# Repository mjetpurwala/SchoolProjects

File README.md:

Project names in each folder

 Baemax: Advanced Embedded Systems Final Project.
   Contents: Pictures and videos of the project and source code

 Alarm Clock: Advanced Embedded Systems Project.
   Contents: Pictures and videos of the project and source code

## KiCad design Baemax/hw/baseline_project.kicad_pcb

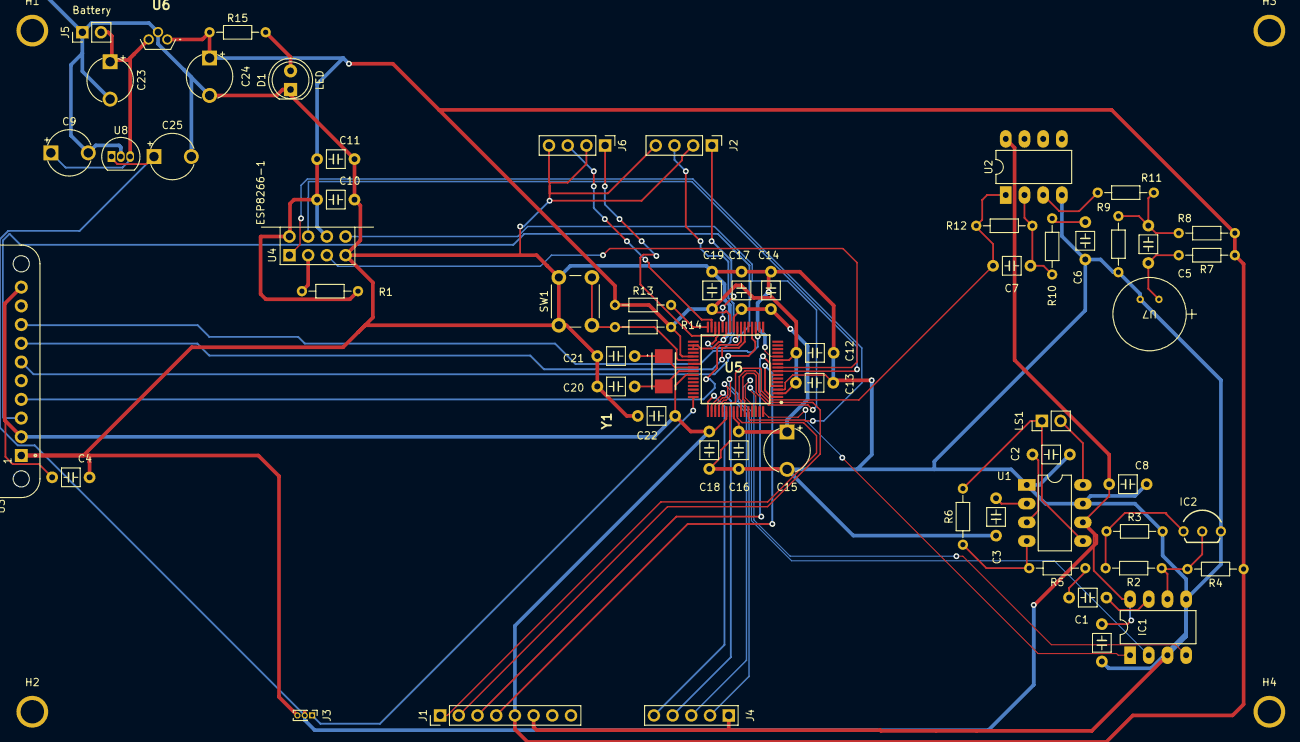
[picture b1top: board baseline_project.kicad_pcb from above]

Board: 2 copper layers, 65 parts (0 on the bottom side), 51 nets.

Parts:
C1, C4, C8, C26: 0.1 uF; C_Axial_200mil
C2: 1.0 uF; C_Axial_200mil
C3, C6: 4.7 uF; C_Axial_200mil
C5: 1u; C_Axial_200mil
C7: 220pF; C_Axial_200mil
C9, C23, C24, C25: 4.7uF; CP_Radial_Tantal200mil
C10: 4.7uF; C_Axial_200mil
C11, C13, C16, C17, C18: 0.1uF; C_Axial_200mil
C12, C19: 0.01uF; C_Axial_200mil
C14, C22: 1uF; C_Axial_200mil
C15: 2.2uF; CP_Radial_Tantal200mil
C20, C21: 10pF C0G; C_Axial_200mil
D1: LED; LED_D5.0mm
H1, H2, H3, H4: MountingHole_4_40
IC1: TLV5616; DIP-8_W7.62mm_LongPads
IC2: LM4041CILPR; ti_LM4041CILPR
J1: Conn_01x06_Pin; PinHeader_1x08_P2.54mm_Vertical
J2, J6: Header_4; PinHeader_1x04_P2.54mm_Vertical
J3: Conn_01x03_Pin; PinHeader_1x03_P1.00mm_Vertical
J4: JTAG; PinHeader_1x05_P2.54mm_Vertical
J5: Battery; PinHeader_1x02_P2.54mm_Vertical
LS1: Speaker; PinHeader_1x02_P2.54mm_Vertical
R1, R7, R14: 10k; R_Axial_DIN0204_L3.6mm_D1.6mm_P7.62mm_Horizontal
R2: 47 kohm; R_Axial_DIN0204_L3.6mm_D1.6mm_P7.62mm_Horizontal
R3, R6: 10 kohm; R_Axial_DIN0204_L3.6mm_D1.6mm_P7.62mm_Horizontal
R4: 2 kohm; R_Axial_DIN0204_L3.6mm_D1.6mm_P7.62mm_Horizontal
R5: 20 kohm; R_Axial_DIN0204_L3.6mm_D1.6mm_P7.62mm_Horizontal
R8, R9: 22k; R_Axial_DIN0204_L3.6mm_D1.6mm_P7.62mm_Horizontal
R10, R11: 1k; R_Axial_DIN0204_L3.6mm_D1.6mm_P7.62mm_Horizontal
R12: 100k; R_Axial_DIN0204_L3.6mm_D1.6mm_P7.62mm_Horizontal
R13: 1M; R_Axial_DIN0204_L3.6mm_D1.6mm_P7.62mm_Horizontal
R15: 330; R_Axial_DIN0204_L3.6mm_D1.6mm_P7.62mm_Horizontal
SW1: Reset; SW_PUSH_6mm
U1: MCP34119P; DIP-8_W7.62mm_LongPads
U2: OPA2350; DIP-8_W7.62mm_LongPads
U3: Adafruit ST7735R; adafruit_st7735r2
U4: ESP8266-1; PinHeader_2x04_P2.54mm_Vertical
U5: TM4C123GH6PMIR; QFP50P1200X1200X160-64N
U6: LP2950-33LPRE3; TL431CLPM
U7: CMA-4544PF-W (elec mic); CMA_CUI_9P7X9P7_CUD
U8: LP2950-5.0_TO92; TO-92_Inline
Y1: ABM3-16.000MHZ-B2-T; ABM3

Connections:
+3V3: C4.1, C10.1, C11.1, C12.1, C13.1, C18.1, C19.1, C22.1, C24.1, J1.5, R1.1, R4.1, R7.1, R8.1, R13.1, R14.1, R15.1, U3.2 (VCC), U3.10 (LITE), U4.6 (Ch_PD), U4.8 (Vcc), U5.2 (VDDA), U5.11 (VDD_1), U5.26 (VDD_2), U5.37 (VBAT), U5.42 (VDD_3), U5.54 (VDD_4), U6.1 (OUTPUT)
+5V: C8.1, C25.1, C26.1, IC1.8 (VDD), J3.2, U1.6 (Vcc), U2.8 (V+), U8.1 (VO)
/LDO: C14.1, C15.1, C16.1, C17.1, U5.25 (VDDC_1), U5.56 (VDDC_2)
/OSC1: C20.1, U5.41 (OSC1), Y1.2
/OSC2: C21.1, U5.40 (OSC0), Y1.1
/Reset: R14.2, SW1.2, U5.38 (~RST)
/TCK: J4.2 (B), U5.52 (PC0/TCK/SWCLK)
/TDI: J4.4 (C), U5.50 (PC2/TDI)
/TDO: J4.5 (C), U5.49 (PC3/TDO/SWO)
/TMS: J4.3 (C), U5.51 (PC1/TMS/SWDIO)
GND: C2.2, C3.2, C4.2, C6.2, C8.2, C9.2, C10.2, C11.2, C12.2, C13.2, C14.2, C15.2, C16.2, C17.2, C18.2, C19.2, C20.2, C21.2, C22.2, C23.2, C24.2, C25.2, C26.2, D1.1 (K), IC1.3 (~CS), IC1.5 (AGND), IC2.3, J1.6, J2.2 (B), J2.4 (C), J3.3, J4.1 (A), J5.1 (A), J6.2 (B), J6.4 (C), R3.2, R9.2, SW1.1, U1.1 (CD), U1.7 (GND), U2.4 (V-), U3.1 (GND), U4.4 (GND), U5.3 (GNDA), U5.12 (GND_1), U5.27 (GND_2), U5.34 (XOSC0), U5.35 (GNDX), U5.39 (GND_3), U5.55 (GND_4), U6.2 (GND), U7.2, U8.2 (GND)
HV: C9.1, C23.1, J5.2 (B), U6.3 (INPUT), U8.3 (VI)
unnamed: C1.2, R5.1
unnamed: C5.1, R7.2, U7.1
unnamed: C5.2, R8.2, R9.1, R11.1
unnamed: C6.1, R10.2
unnamed: D1.2 (A), R15.2
unnamed: C1.1, IC1.7 (OUT)
unnamed: IC1.6 (REF), IC2.2, R2.1, R4.2
unnamed: IC2.1, R2.2, R3.1
unnamed: C2.1, U1.3 (FC1)
unnamed: C3.1, U1.2 (FC2)
unnamed: R5.2, R6.1, U1.4 (VIN)
unnamed: LS1.1, R6.2, U1.5 (VO1)
unnamed: LS1.2, U1.8 (VO2)
unnamed: R11.2, U2.3 (+)
unnamed: C7.1, R10.1, R12.1, U2.2 (-)
unnamed: R1.2, U4.2 (GPIO0)
unnamed: R13.2, U5.32 (~WAKE)
PA2: U3.8 (SCK), U5.19 (PA2/SSI0C1K)
PA3: U3.6 (TFT_CS), U5.20 (PA3/SSI0FSS)
PA5: U3.7 (MOSI), U5.22 (PA5/SSI0TX)
PA6: U3.4 (D/C), U5.23 (PA6)
PA7: U3.3 (RESET), U5.24 (PA7)
PB3: J3.1, U5.48 (PB3/I2C0SDA)
PB4: J1.2, U5.58 (PB4)
PB5: J1.1, U5.57 (PB5)
PB6: J1.4, U5.1 (PB6)
PB7: J1.3, U5.4 (PB7)
PD0: IC1.2 (SCLK), U5.61 (PD0)
PD1: IC1.4 (FS), U5.62 (PD1)
PD3: IC1.1 (DIN), U5.64 (PD3)
PD6: C7.2, R12.2, U2.1, U5.53 (PD6)
PE0: U4.3 (GPIO2), U5.9 (PE0)
PE1: U4.7 (Reset), U5.8 (PE1)
PE4: U4.5 (TxD), U5.59 (PE4)
PE5: U4.1 (RxD), U5.60 (PE5)
PF0: J2.1 (A), U5.28 (PF0)
PF1: J2.3 (C), U5.29 (PF1)
PF2: J6.1 (A), U5.30 (PF2)
PF3: J6.3 (C), U5.31 (PF3)

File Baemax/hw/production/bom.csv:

Designator,Footprint,Quantity,Value,LCSC Part #
"C1, C26, C4, C8",C_Axial_200mil,4,0.1 uF,
C10,C_Axial_200mil,1,4.7uF,
"C11, C13, C16, C17, C18",C_Axial_200mil,5,0.1uF,
"C12, C19",C_Axial_200mil,2,0.01uF,
"C14, C22",C_Axial_200mil,2,1uF,
C15,CP_Radial_Tantal200mil,1,2.2uF,
C2,C_Axial_200mil,1,1.0 uF,
"C20, C21",C_Axial_200mil,2,10pF C0G,
"C23, C24, C25, C9",CP_Radial_Tantal200mil,4,4.7uF,
"C3, C6",C_Axial_200mil,2,4.7 uF,
C5,C_Axial_200mil,1,1u,
C7,C_Axial_200mil,1,220pF,
D1,LED_D5.0mm,1,LED,
"H1, H2, H3, H4",MountingHole_4_40,4,~,
IC1,DIP-8_W7.62mm_LongPads,1,TLV5616,
IC2,ti_LM4041CILPR,1,LM4041CILPR,
J1,PinHeader_1x08_P2.54mm_Vertical,1,Conn_01x06_Pin,
"J2, J6",PinHeader_1x04_P2.54mm_Vertical,2,Header_4,
J3,PinHeader_1x03_P1.00mm_Vertical,1,Conn_01x03_Pin,
J4,PinHeader_1x05_P2.54mm_Vertical,1,JTAG,
J5,PinHeader_1x02_P2.54mm_Vertical,1,Battery,
LS1,PinHeader_1x02_P2.54mm_Vertical,1,Speaker,
"R1, R14, R7",R_Axial_DIN0204_L3.6mm_D1.6mm_P7.62mm_Horizontal,3,10k,
"R10, R11",R_Axial_DIN0204_L3.6mm_D1.6mm_P7.62mm_Horizontal,2,1k,
R12,R_Axial_DIN0204_L3.6mm_D1.6mm_P7.62mm_Horizontal,1,100k,
R13,R_Axial_DIN0204_L3.6mm_D1.6mm_P7.62mm_Horizontal,1,1M,
R15,R_Axial_DIN0204_L3.6mm_D1.6mm_P7.62mm_Horizontal,1,330,
R2,R_Axial_DIN0204_L3.6mm_D1.6mm_P7.62mm_Horizontal,1,47 kohm,
"R3, R6",R_Axial_DIN0204_L3.6mm_D1.6mm_P7.62mm_Horizontal,2,10 kohm,
R4,R_Axial_DIN0204_L3.6mm_D1.6mm_P7.62mm_Horizontal,1,2 kohm,
R5,R_Axial_DIN0204_L3.6mm_D1.6mm_P7.62mm_Horizontal,1,20 kohm,
"R8, R9",R_Axial_DIN0204_L3.6mm_D1.6mm_P7.62mm_Horizontal,2,22k,
SW1,SW_PUSH_6mm,1,Reset,
U1,DIP-8_W7.62mm_LongPads,1,MCP34119P,
U2,DIP-8_W7.62mm_LongPads,1,OPA2350,
U3,adafruit_st7735r2,1,Adafruit ST7735R,
U4,PinHeader_2x04_P2.54mm_Vertical,1,ESP8266-1,
U5,QFP50P1200X1200X160-64N,1,TM4C123GH6PMIR,
U6,TL431CLPM,1,LP2950-33LPRE3,
U7,CMA_CUI_9P7X9P7_CUD,1,CMA-4544PF-W (elec mic),
U8,TO-92_Inline,1,LP2950-5.0_TO92,
Y1,ABM3,1,ABM3-16.000MHZ-B2-T,

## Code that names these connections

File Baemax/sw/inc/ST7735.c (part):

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// Runs on LM4F120/TM4C123
// Low level drivers for the ST7735 160x128 LCD based off of
// the file described above.  Further modified for simultaneous
// use of the SD card (CS on PD7) and ST7735 LCD (CS on PA3).
//    16-bit color, 128 wide by 160 high LCD
// Daniel Valvano
// April 1, 2016
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// ST7735
// Backlight (pin 10) connected to +3.3 V
// MISO (pin 9) connected to PA4 (SSI0Rx)
// SCK (pin 8) connected to PA2 (SSI0Clk)
// MOSI (pin 7) connected to PA5 (SSI0Tx)
// TFT_CS (pin 6) connected to PA3 (GPIO/SSI0Fss)
// CARD_CS (pin 5) connected to PD7 or PB0 (GPIO)
// Data/Command (pin 4) connected to PA6 (GPIO), high for data, low for command
// RESET (pin 3) connected to PA7 (GPIO)
// VCC (pin 2) connected to +3.3 V
// Gnd (pin 1) connected to ground

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// Silkscreen Label (SDC side up; LCD side down) - Connection
// VCC  - +3.3 V
// GND  - Ground
// !SCL - PA2 Sclk SPI clock from microcontroller to TFT or SDC
// !SDA - PA5 MOSI SPI data from microcontroller to TFT or SDC
// DC   - PA6 TFT data/command
// RES  - PA7 TFT reset
// CS   - PA3 TFT_CS, active low to enable TFT
// *CS  - PD7 or PB0 SDC_CS, active low to enable SDC
// MISO - PA4 MISO SPI data from SDC to microcontroller
// SDA  ? (NC) I2C data for ADXL345 accelerometer
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#define SDC_CS_PB5 1
#define SDC_CS_PD7 0

// SDC CS is PD7 or PB0 , TFT CS is PA3
// to change CS to another GPIO, change SDC_CS and CS_Init
// **********ST7735 TFT and SDC*******************
// ST7735
// 1  ground
// 2  Vcc +3.3V
// 3  PA7 TFT reset      -> PD6
// 4  PA6 TFT data/command    -> PD1
// 5  PD7/PB0 SDC_CS, active low to enable SDC  ->PD7
// 6  PA3 TFT_CS, active low to enable TFT  
// 7  PA5 MOSI SPI data from microcontroller to TFT or SDC
// 8  PA2 Sclk SPI clock from microcontroller to TFT or SDC
// 9  PA4 MOSO SPI data from SDC to microcontroller
// 10 Light, backlight connected to +3.3 V

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// Silkscreen Label (SDC side up; LCD side down) - Connection
// VCC  - +3.3 V
// GND  - Ground
// !SCL - PA2 Sclk SPI clock from microcontroller to TFT or SDC
// !SDA - PA5 MOSI SPI data from microcontroller to TFT or SDC
// DC   - PA6 TFT data/command
// RES  - PA7 TFT reset
// CS   - PA3 TFT_CS, active low to enable TFT
// *CS  - PD7/PB0 SDC_CS, active low to enable SDC
// MISO - PA4 MISO SPI data from SDC to microcontroller
// SDA  ? (NC) I2C data for ADXL345 accelerometer
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// Backlight + - Light, backlight connected to +3.3 V

#define TFT_CS           (*((volatile uint32_t *)0x40004020))
#define TFT_CS_LOW       0 // CS controlled by software PA3
#define TFT_CS_HIGH      0x08
#if SDC_CS_PD7
// PD7 output used for SDC CS
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  SDC_CS = SDC_CS_HIGH;
}
#endif
// PB5 output used for SDC CS
#if SDC_CS_PB5
#define SDC_CS           (*((volatile uint32_t *)0x40005080))
#define SDC_CS_LOW       0           // CS controlled by software
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void SDC_CS_Init(void){
	SYSCTL_RCGCGPIO_R |= 0x02;            // activate clock for Port B
  while((SYSCTL_PRGPIO_R&0x02) == 0){}; // allow time for clock to stabilize
  GPIO_PORTB_DIR_R |= 0x20;             // make PB5 out
  GPIO_PORTB_AFSEL_R &= ~0x20;          // disable alt funct on PB5
  GPIO_PORTB_DR4R_R |= 0x20;            // 4mA drive on outputs
  GPIO_PORTB_PUR_R |= 0x20;             // enable weak pullup on PB5
  GPIO_PORTB_DEN_R |= 0x20;             // enable digital I/O on PB5
                                        // configure PB5 as GPIO
  GPIO_PORTB_PCTL_R = (GPIO_PORTB_PCTL_R&0xFF0FFFFF)+0x00000000;
  GPIO_PORTB_AMSEL_R &= ~0x20;          // disable analog functionality on PB0
  SDC_CS = SDC_CS_HIGH;
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		
		
		
  GPIO_PORTA_DIR_R |= 0xC8;             // make PA3,6,7 out
  GPIO_PORTA_AFSEL_R &= ~0xC8;          // disable alt funct on PA3,6,7
  GPIO_PORTA_DEN_R |= 0xC8;             // enable digital I/O on PA3,6,7
                                        // configure PA3,6,7 as GPIO
		
		
  GPIO_PORTA_PCTL_R = (GPIO_PORTA_PCTL_R&0x00FF0FFF)+0x00000000;
  GPIO_PORTA_AMSEL_R &= ~0xC8;          // disable analog functionality on PA3,6,7
  TFT_CS = TFT_CS_LOW;
  RESET = RESET_HIGH;
  Delay1ms(500);
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  Delay1ms(500);

  // initialize SSI2
  GPIO_PORTB_AFSEL_R |= 0xD0;           // enable alt funct on PB4,6,7
	GPIO_PORTA_PUR_R |= 0x08;             // enable weak pullup on PA3
  GPIO_PORTB_PUR_R |= 0xD0;             // enable weak pullup on PB4,6,7
  GPIO_PORTB_DEN_R |= 0xD0;             // enable digital I/O on PB4,6,7
	
                                        // configure PB4,6,7 as SSI
  GPIO_PORTB_PCTL_R = (GPIO_PORTB_PCTL_R&0x00F0FFFF)+0x22020000;
  GPIO_PORTB_AMSEL_R &= ~0xD0;          // disable analog functionality on PB4,6,7
	
	//DONT FORGET THIS ILL KILL MYSEWLF
  SDC_CS_Init();                        // SDC CS on PB0 or PD7
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
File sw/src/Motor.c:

#include "../inc/tm4c123gh6pm.h"
#include "../inc/CortexM.h"
#include <stdint.h>

/************ MotorDriver_Init ************/
/*
Pin Mappings: 
PWMA -> PF2
PWMB -> PF3
AIN1 -> PA2
AIN2 -> PA5
BIN1 -> PF0
BIN2 -> PF1
STBY -> PD6
*/
void MotorDriver_Init(void){
	// Turn on Clock and PWM Module 1
	SYSCTL_RCGCGPIO_R |= 0x29; 											// check to make sure this is Ports A, D, and F!!!!!
	SYSCTL_RCGCPWM_R |= 0x02;
	while ((SYSCTL_PRGPIO_R & 0x29) == 0) {}
		
	// Set PA2 and PA5 for AIN1 and AIN2 
	GPIO_PORTA_DIR_R |= 0x24;
	GPIO_PORTA_DEN_R |= 0x24;
		
	GPIO_PORTF_LOCK_R = 0x4C4F434B;  // Unlock Port F
	GPIO_PORTF_CR_R |= 0x01;         // Allow changes to PF0
	//GPIO_PORTF_AMSEL_R &= ~0x01; // Disable analog mode
	//GPIO_PORTF_AFSEL_R &= ~0x01; // Disable alternate functions
	//GPIO_PORTF_PCTL_R &= ~0x0000000F; // Configure as GPIO
	GPIO_PORTF_PUR_R |= 0x01;  // Enable pull-up for PF0
		
	// Set PF0 and PF1 for BIN1 and BIN2
	GPIO_PORTF_DIR_R |= 0x03;
	GPIO_PORTF_DEN_R |= 0x03; 

	// Set PD6 as output for STBY
	GPIO_PORTD_DIR_R |= 0x40;
	GPIO_PORTD_DEN_R |= 0x40;
	
	// Set PF2 and PF3 for PWMA and PWMB
	GPIO_PORTF_AFSEL_R |= 0x0C;     			// enable alt funct on PF3 PF2
  GPIO_PORTF_PCTL_R = (GPIO_PORTF_PCTL_R&0xFFFFF00FF)|0x00005500;
    // PF2 is M1PWM6
    // PF3 is M1PWM7
  GPIO_PORTF_DIR_R |= 0x0C;             // PF3 PF2 output
  GPIO_PORTF_DEN_R |= 0x0C;             // enable digital I/O on PF3 PF2
  GPIO_PORTF_DR8R_R |= 0x0C;            // high current output on PF3 PF2
    // bit 20=1 for USEPWMDIV
    // bits 19-17 = 0 for divide by 2
    // bits 19-17 = n for divide by 2*(2^n)
    // bits 19-17 = 3 for divide by 16
    // bits 19-17 = 5 for divide by 64
  SYSCTL_RCC_R = 0x00120000 |           // 3) use PWM divider 
      (SYSCTL_RCC_R & (~0x000E0000));   //    configure for /4 divider
  PWM1_3_CTL_R = 0;                     // 4) re-loading down-counting mode
	
  PWM1_3_GENA_R = 0xC8;                 // low on LOAD, high on CMPA down
  // PF2 goes low on LOAD
  // PF2 goes high on CMPA down
  PWM1_3_LOAD_R = 40000 - 1;    				// 5) cycles needed to count down to 0
  PWM1_3_CMPA_R = 0;                  	// 6) count value when output rises
    
  PWM1_3_GENB_R = 0xC08;               	// low on LOAD, high on CMPB down
  // PF3 goes low on LOAD
  // PF3 goes high on CMPB down  
  PWM1_3_CMPB_R = 0;                   	// 6) count value when output rises
  PWM1_3_CTL_R |= 0x00000001;           // 7) start PWM1
  PWM1_ENABLE_R |= 0x000000C0;          // enable PF2 is M1PWM6 and PF3 is M1PWM7

}

// Initialize SysTick with busy wait running at bus clock.
void SysTick_Init(void){
    // ECE319K students write this function
		NVIC_ST_CTRL_R = 0; // 1) disable SysTick during setup 
		NVIC_ST_RELOAD_R = 0x00FFFFFF; // 2) maximum reload value 
		NVIC_ST_CURRENT_R = 0; // 3) any write to CURRENT clears it 
		NVIC_ST_CTRL_R = 0x00000005; // 4) enable SysTick with core clock

}
// The delay parameter is in units of the 80 MHz core clock. (12.5 ns)
void SysTick_Wait(uint32_t delay){
  // ECE319K students write this function
	NVIC_ST_RELOAD_R = delay-1;  // number of counts
  NVIC_ST_CURRENT_R = 0;       // any value written to CURRENT clears
  while((NVIC_ST_CTRL_R&0x00010000)==0){ // wait for COUNT flag
  }

}
// 1000us equals 1ms
void SysTick_Wait1ms(uint32_t delay){
    // ECE319K students write this function
		for(uint32_t i=0; i<delay; i++){
		SysTick_Wait(80000); // wait 1 ms
		}
}

void MotorStop(char select){
	if(select == 'A'){
		PWM1_3_CMPA_R = 0;
	}else if(select == 'B'){
		PWM1_3_CMPB_R = 0;
	}else{
		PWM1_3_CMPA_R = 0;
		PWM1_3_CMPB_R = 0;
	}
	SysTick_Wait1ms(1000);       
}

void MotorForward(char select, uint32_t duty, uint32_t delay){
	if(select == 'A'){
		GPIO_PORTA_DATA_R |= 0x04;  	// Set PA2 (AIN1) high
		GPIO_PORTA_DATA_R &= ~0x20; 	// Set PA5 (AIN2) low
		PWM1_3_CMPA_R = duty;      		// Set PWMA duty cycle
	}else if(select == 'B'){
		GPIO_PORTF_DATA_R |= 0x01;  	// Set PF0 (BIN1) high
    GPIO_PORTF_DATA_R &= ~0x02; 	// Set PF1 (BIN2) low
    PWM1_3_CMPB_R = duty;      		// Set PWMB duty cycle
	}else{
		GPIO_PORTA_DATA_R |= 0x04;  	// Set PA2 (AIN1) high
		GPIO_PORTA_DATA_R &= ~0x20; 	// Set PA5 (AIN2) low
		PWM1_3_CMPA_R = duty;      		// Set PWMA duty cycle
		GPIO_PORTF_DATA_R |= 0x01;  	// Set PF0 (BIN1) high
    GPIO_PORTF_DATA_R &= ~0x02; 	// Set PF1 (BIN2) low
    PWM1_3_CMPB_R = duty;      		// Set PWMB duty cycle
	}
	SysTick_Wait1ms(delay);
	MotorStop(select);
}

void MotorBackward(char select, uint32_t duty, uint32_t delay){
	if(select == 'A'){
		GPIO_PORTA_DATA_R &= ~0x04; 	// Set PA2 (AIN1) low
    GPIO_PORTA_DATA_R |= 0x20;  	// Set PA3 (AIN2) high
    PWM1_3_CMPA_R = duty;       	// Set PWMA duty cycle
	}else if(select == 'B'){
		GPIO_PORTF_DATA_R &= ~0x01; 	// Set PF0 (BIN1) low
    GPIO_PORTF_DATA_R |= 0x02;  	// Set PF1 (BIN2) high
    PWM1_3_CMPB_R = duty;       	// Set PWMB duty cycle
	}else{
		GPIO_PORTA_DATA_R &= ~0x04; 	// Set PA2 (AIN1) low
    GPIO_PORTA_DATA_R |= 0x20;  	// Set PA3 (AIN2) high
    PWM1_3_CMPA_R = duty;       	// Set PWMA duty cycle
		GPIO_PORTF_DATA_R &= ~0x01; 	// Set PF0 (BIN1) low
    GPIO_PORTF_DATA_R |= 0x02;  	// Set PF1 (BIN2) high
    PWM1_3_CMPB_R = duty;       	// Set PWMB duty cycle
	}
	SysTick_Wait1ms(delay);
	MotorStop(select);
}

void MotorSequenceTest(void) {
	// Activate motor driver
	GPIO_PORTD_DATA_R |= 0x40; 				// Setting STBY to high to turn on motor driver

	// Motor A Test
	MotorForward('A', 12000, 2000);		// Test 1: Direction: Forward, Duty Cycle: 75%, Duration: 2s
	MotorBackward('A', 8000, 2000);		// Test 2: Direction: Backward, Duty Cycle: 50%, Duration: 2s

	// Motor B Test
	MotorForward('B', 12000, 2000);		// Test 3: Direction: Forward, Duty Cycle: 75%, Duration: 2s
  MotorBackward('B', 8000, 2000);		// Test 4: Direction: Backward, Duty Cycle: 50%, Duration: 2s

	// Deactivate motor driver
  GPIO_PORTD_DATA_R &= ~0x40; 			// Seting STBY to low to turn off motor driver
}

void RightMotorHi(void){
	GPIO_PORTD_DATA_R |= 0x40;
	MotorForward('A', 30000, 1000);
	MotorBackward('A', 30000, 1000);
	GPIO_PORTD_DATA_R &= ~0x40;
}


void FlurryFight(void){
	GPIO_PORTD_DATA_R |= 0x40;
	MotorForward('C', 36000, 2000);
	// calibrate MotorBackward if needed
	GPIO_PORTD_DATA_R &= ~0x40;
}

void RightPunch(void){
	GPIO_PORTD_DATA_R |= 0x40;
	MotorForward('A', 36000, 2000);
	MotorBackward('A', 3600, 1000);
	GPIO_PORTD_DATA_R &= ~0x40;
}

void LeftPunch(void){
	GPIO_PORTD_DATA_R |= 0x40;
	MotorForward('B', 36000, 2000);
	MotorBackward('B', 3600, 1000);
	GPIO_PORTD_DATA_R &= ~0x40;
}

void Hug4U(void){
	GPIO_PORTD_DATA_R |= 0x40;
	MotorForward('C', 25000, 1000);
	MotorBackward('C', 25000, 1000);
	GPIO_PORTD_DATA_R &= ~0x40;
}

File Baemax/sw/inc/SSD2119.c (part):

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//
//  Control pin assignments:
//  PA4     RD  Read control signal             -------------------------
//  PA5     WR  Write control signal            | PA7 | PA6 | PA5 | PA4 |
//  PA6     RS  Register/Data select signal     | CS  | RS  | WR  | RD  |
//  PA7     CS  Chip select signal              -------------------------
//
//  Touchpad pin assignments:
//  PA2     Y-                                  -------------  -------------
//  PA3     X-                                  | PA3 | PA2 |  | PE5 | PE4 |
//  PE4     X+    AIN9                          | X-  | Y-  |  | Y+  | X+  |
//  PE5     Y+    AIN8                          -------------  -------------
//   
//  Touchscreen resistance measurements:
//  -------------------             
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
// bit-banded addresses for port stuff
#define LCD_RD_PIN       (*((volatile unsigned long *)0x40004040))     // PA4
#define LCD_WR_PIN       (*((volatile unsigned long *)0x40004080))     // PA5
#define LCD_RS_PIN       (*((volatile unsigned long *)0x40004100))     // PA6
#define LCD_CS_PIN       (*((volatile unsigned long *)0x40004200))     // PA7
#define LCD_CTRL         (*((volatile unsigned long *)0x400043C0))     // PA4-7
#define LCD_DATA         (*((volatile unsigned long *)0x400053FC))     // PB0-7
// ************** ADC_Init *********************************
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// - RS low during command write
// ********************************************************
//  PA4     RD  Read control signal             -------------------------
//  PA5     WR  Write control signal            | PA7 | PA6 | PA5 | PA4 |
//  PA6     RS  Register/Data select signal     | CS  | RS  | WR  | RD  |
//  PA7     CS  Chip select signal              -------------------------
void LCD_WriteCommand(unsigned char data){volatile unsigned long delay;
    LCD_CTRL = 0x30;  // Set CS=0, RS=0, WR=1, RD=1
    LCD_DATA = 0x00;  // Write 0 as MSB of command data
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// - RS high during data write
// ********************************************************
//  PA4     RD  Read control signal             -------------------------
//  PA5     WR  Write control signal            | PA7 | PA6 | PA5 | PA4 |
//  PA6     RS  Register/Data select signal     | CS  | RS  | WR  | RD  |
//  PA7     CS  Chip select signal              -------------------------
void LCD_WriteData(unsigned short data){volatile unsigned long delay;
    LCD_CTRL = 0x70; // CS low
    LCD_DATA = (data >> 8); // Write MSB to LCD data bus
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        }
    }
}
#define TOUCH_YN       (*((volatile unsigned long *)0x40004010))     // PA2
#define TOUCH_XP       (*((volatile unsigned long *)0x40004020))     // PA3
#define TOUCH_XN       (*((volatile unsigned long *)0x40024040))     // PE4 / AIN9
#define TOUCH_YP       (*((volatile unsigned long *)0x40024080))     // PE5 / AIN8

#define PA2     0x04
#define PA3     0x08
#define PE4     0x10
#define PE5     0x20

#define NUM_SAMPLES 4
#define NUM_VALS_TO_AVG 8
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//unsigned char numVals = 0;


//         YP / PE5 / AIN8
//      ---------------------
//      |                   |    
//   XP |                   | XN  
//  PA3 |                   | PE4
//      |                   | AIN9
//      |                   |
//      |                   |
//      ---------------------
//             YN / PA2



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    wait++;
    wait++;

//    // Configure PA2/PA3 for GPIO digital output
    GPIO_PORTA_DIR_R    |=  0x0C;
//    GPIO_PORTA_AFSEL_R  &= ~0x0C;
//    GPIO_PORTA_DEN_R    |=  0x0C;   
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    wait++;
    wait++;
    
//    // Configure PE4/PE5 for GPIO digital output
    GPIO_PORTE_DIR_R    |=  0x30;
//    GPIO_PORTE_AFSEL_R  &= ~0x30;
//    GPIO_PORTE_DEN_R    |=  0x30;
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    long sum = 0;
    long result = 0;
    
    GPIO_PORTA_DATA_R   &= ~PA2;

    // Configure PA3 (XP) for GPIO HIGH
    GPIO_PORTA_AFSEL_R  &= ~PA3;       // ASFEL = 0
    GPIO_PORTA_DEN_R    |=  PA3;       // DEN = 1
    GPIO_PORTA_DIR_R    |=  PA3;       // DIR = 1
    GPIO_PORTA_DATA_R   |=  PA3;       // DATA = 1
    
    // Configure PE4 (XN) for GPIO LOW
    GPIO_PORTE_AFSEL_R  &= ~PE4;       // ASFEL = 0
    GPIO_PORTE_DEN_R    |=  PE4;       // DEN = 1
    GPIO_PORTE_DIR_R    |=  PE4;       // DIR = 1
    GPIO_PORTE_DATA_R   &= ~PE4;       // DATA = 0
    
    // Configure PA2 (YN) for analog hi-Z
    GPIO_PORTA_AFSEL_R  &= ~PA2;       // AFSEL = 0
    GPIO_PORTA_DEN_R    &= ~PA2;       // DEN = 0
    GPIO_PORTA_DIR_R    &= ~PA2;       // DIR = 0
    
    // Configure PE5 (YP) for ADC use
    GPIO_PORTE_AFSEL_R  |=  PE5;       // AFSEL = 1
    GPIO_PORTE_DEN_R    &= ~PE5;       // DEN = 0
    GPIO_PORTE_AMSEL_R  |=  PE5;       // AMSEL = 1
   
    // Configure ADC to read from AIN8 (PE5, YP)
    ADC_SetChannel(8);
    
    // Take some samples to average
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        sum += ADC_Read();
    }

    GPIO_PORTE_AMSEL_R  &= ~PE5;       // AMSEL = 0
     
    // Compute average
    result = sum / NUM_SAMPLES;
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    long sum = 0;
    long result = 0;

    // Configure PE5 (YP) for GPIO HIGH
    GPIO_PORTE_AFSEL_R  &= ~PE5;       // ASFEL = 0
    GPIO_PORTE_DEN_R    |=  PE5;       // DEN = 1
    GPIO_PORTE_DIR_R    |=  PE5;       // DIR = 1
    GPIO_PORTE_DATA_R   |=  PE5;       // DATA = 1
    //TOUCH_XP = 0xFF;
    
    // Configure PA2 (YN) for GPIO LOW
    GPIO_PORTA_AFSEL_R  &= ~PA2;       // ASFEL = 0
    GPIO_PORTA_DEN_R    |=  PA2;       // DEN = 1
    GPIO_PORTA_DIR_R    |=  PA2;       // DIR = 1
    GPIO_PORTA_DATA_R   &= ~PA2;       // DATA = 0
    
    // Configure PA3 (XP) for analog hi-Z
    GPIO_PORTA_AFSEL_R  &= ~PA3;       // AFSEL = 0
    GPIO_PORTA_DEN_R    &= ~PA3;       // DEN = 0
    GPIO_PORTA_DIR_R    &= ~PA3;       // DIR = 0
    
    // Configure PE4 (XN) for ADC use
    GPIO_PORTE_AFSEL_R  |=  PE4;       // AFSEL = 1
    GPIO_PORTE_DEN_R    &= ~PE4;       // DEN = 0
    GPIO_PORTE_AMSEL_R  |=  PE4;       // AMSEL = 1
   
    // Configure ADC to read from AIN9 (PE4, XN)
    ADC_SetChannel(9);
    
    // Take some samples to average
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    long sum = 0;
    long result = 0;

    // Configure PA2 (YN) for GPIO HIGH
    GPIO_PORTA_AFSEL_R  &= ~PA2;       // ASFEL = 0
    GPIO_PORTA_DEN_R    |=  PA2;       // DEN = 1
    GPIO_PORTA_DIR_R    |=  PA2;       // DIR = 1
    GPIO_PORTA_DATA_R   |=  PA2;       // DATA = 1
    
    // Configure PA3 (XP) for GPIO LOW
    GPIO_PORTA_AFSEL_R  &= ~PA3;       // ASFEL = 0
    GPIO_PORTA_DEN_R    |=  PA3;       // DEN = 1
    GPIO_PORTA_DIR_R    |=  PA3;       // DIR = 1
    GPIO_PORTA_DATA_R   &= ~PA3;       // DATA = 0
    
    // Configure PE5 (YP) for analog hi-Z
    GPIO_PORTE_AFSEL_R  &= ~PE5;       // AFSEL = 0
    GPIO_PORTE_DEN_R    &= ~PE5;       // DEN = 0
    GPIO_PORTE_DIR_R    &= ~PE5;       // DIR = 0
    
    // Configure PE4 (XN) for ADC use
    GPIO_PORTE_AMSEL_R  |=  PE4;       // AMSEL = 1
    GPIO_PORTE_AFSEL_R  |=  PE4;       // AFSEL = 1
    GPIO_PORTE_DEN_R    &= ~PE4;       // DEN = 0
    //GPIO_PORTE_DIR_R    &= ~PE4;       // DIR = 0    

    // Configure ADC to read from AIN9 (PE4, XN)
    ADC_SetChannel(9);
    
    // Take some samples to average
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    long sum = 0;
    long result = 0;

    // Configure PA2 (YN) for GPIO HIGH
    GPIO_PORTA_AFSEL_R  &= ~PA2;       // ASFEL = 0
    GPIO_PORTA_DEN_R    |=  PA2;       // DEN = 1
    GPIO_PORTA_DIR_R    |=  PA2;       // DIR = 1
    GPIO_PORTA_DATA_R   |=  PA2;       // DATA = 1
    
    // Configure PA3 (XP) for GPIO LOW
    GPIO_PORTA_AFSEL_R  &= ~PA3;       // ASFEL = 0
    GPIO_PORTA_DEN_R    |=  PA3;       // DEN = 1
    GPIO_PORTA_DIR_R    |=  PA3;       // DIR = 1
    GPIO_PORTA_DATA_R   &= ~PA3;       // DATA = 0
    
    // Configure PE4 (XN) for analog hi-Z
    GPIO_PORTE_AFSEL_R  &= ~PE4;       // AFSEL = 0
    GPIO_PORTE_DEN_R    &= ~PE4;       // DEN = 0
    GPIO_PORTE_DIR_R    &= ~PE4;       // DIR = 0
    GPIO_PORTE_AMSEL_R  &= ~PE4;       // AMSEL = 0
    
    // Configure PE5 (YP) for ADC use
    GPIO_PORTE_AFSEL_R  |=  PE5;       // AFSEL = 1
    GPIO_PORTE_DEN_R    &= ~PE5;       // DEN = 0
    GPIO_PORTE_DIR_R    &= ~PE5;       // DIR = 0
    GPIO_PORTE_AMSEL_R  |=  PE5;       // AMSEL = 1
   
    // Configure ADC to read from AIN9 (PE5, YP)
    ADC_SetChannel(8);
    
    // Take some samples to average
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    // Set YN low
    TOUCH_YN = 0x00;
    
    // Configure XN (PA3) for digital input
    GPIO_PORTA_DIR_R &= ~0x08;
    
    // Configure YP (PE5) for analog Hi-Z
    GPIO_PORTE_DIR_R &= ~0x20;
    GPIO_PORTE_DEN_R &= ~0x20;
   
    // Setup falling edge interrupt on XN (PA3)
    GPIO_PORTA_PUR_R |=  0x08;   // enable weak pull up
    GPIO_PORTA_IS_R  &= ~0x08;     // (d) PF4 is edge-sensitive
    GPIO_PORTA_IBE_R &= ~0x08;    //     PF4 is not both edges
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
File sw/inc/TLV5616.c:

// TLV5616.c
// Runs on TM4C123
// Use SSI1 to send a 16-bit code to the TLV5616 and return the reply.
// Daniel Valvano
// EE445L Fall 2015
//    Jonathan W. Valvano 9/22/15

/* This example accompanies the book
   "Embedded Systems: Real Time Interfacing to ARM Cortex M Microcontrollers",
   ISBN: 978-1463590154, Jonathan Valvano, copyright (c) 2014

 Copyright 2014 by Jonathan W. Valvano, valvano@mail.utexas.edu
    You may use, edit, run or distribute this file
    as long as the above copyright notice remains
 THIS SOFTWARE IS PROVIDED "AS IS".  NO WARRANTIES, WHETHER EXPRESS, IMPLIED
 OR STATUTORY, INCLUDING, BUT NOT LIMITED TO, IMPLIED WARRANTIES OF
 MERCHANTABILITY AND FITNESS FOR A PARTICULAR PURPOSE APPLY TO THIS SOFTWARE.
 VALVANO SHALL NOT, IN ANY CIRCUMSTANCES, BE LIABLE FOR SPECIAL, INCIDENTAL,
 OR CONSEQUENTIAL DAMAGES, FOR ANY REASON WHATSOEVER.
 For more information about my classes, my research, and my books, see
 http://users.ece.utexas.edu/~valvano/
 */

// SSIClk (SCLK) connected to PD0
// SSIFss (FS)   connected to PD1
// SSITx (DIN)   connected to PD3

#include <stdint.h>
#include "../inc/tm4c123gh6pm.h"

//----------------   DAC_Init     -------------------------------------------
// Initialize TLV5616 12-bit DAC
// assumes bus clock is 80 MHz
// inputs: initial voltage output (0 to 4095)
// outputs:none
void DAC_Init(uint16_t data){
    // write this
	  // Consider the following registers:
	  // SYSCTL_RCGCSSI_R, SSI1_CR1_R, SSI1_CPSR_R, SSI1_CR0_R, SSI1_DR_R, SSI1_CR1_R
		// initialize SSI1
		// will need to turn on port d clock
		SYSCTL_RCGCSSI_R |= 0x02;  // activate SSI1
		SYSCTL_RCGCGPIO_R |= 0x08; // activate port D
		while((SYSCTL_PRGPIO_R&0x08)==0){}; // allow time for clock to start

		// toggle RST low to reset; CS low so it'll listen to us
		// SSI0Fss is temporarily used as GPIO
		
		GPIO_PORTD_AFSEL_R |= 0xB;           // enable alt funct on PD 0,1,3
		GPIO_PORTD_DEN_R |= 0xB;             // enable digital I/O on PD 0,1,2
																					// configure PD 0,1,2 as SSI
		GPIO_PORTD_PCTL_R = (GPIO_PORTD_PCTL_R&0xFFFF0F00)+0x00002022;
		GPIO_PORTD_AMSEL_R &= ~0xB;          // disable analog functionality on PA2,3,5
		SSI1_CR1_R &= ~SSI_CR1_SSE;           // disable SSI
		SSI1_CR1_R &= ~SSI_CR1_MS;            // master mode
																					// configure for system clock/PLL baud clock source
		SSI1_CC_R = (SSI1_CC_R&~SSI_CC_CS_M)+SSI_CC_CS_SYSPLL;
	//                                        // clock divider for 3.125 MHz SSIClk (50 MHz PIOSC/16)
	//  SSI0_CPSR_R = (SSI0_CPSR_R&~SSI_CPSR_CPSDVSR_M)+16;
																					// clock divider for 8 MHz SSIClk (80 MHz PLL/24)
																					// SysClk/(CPSDVSR*(1+SCR))
																					// 80/(10*(1+0)) = 8 MHz (slower than 4 MHz)
		SSI1_CPSR_R = (SSI1_CPSR_R&~SSI_CPSR_CPSDVSR_M)+4; // must be even number
		SSI1_CR0_R &= ~(SSI_CR0_SCR_M);      // SCR = 0 (8 Mbps data rate)
										      // SPH = 0
		SSI1_CR0_R &= ~(SSI_CR0_SPH);					//SPH = 0
		SSI1_CR0_R |=	(SSI_CR0_SPO);         // SPO = 1
																					// FRF = TI format
		SSI1_CR0_R = (SSI1_CR0_R&~SSI_CR0_FRF_M)+SSI_CR0_FRF_TI;
																					// DSS = 16-bit data
		SSI1_CR0_R = (SSI1_CR0_R&~SSI_CR0_DSS_M)+SSI_CR0_DSS_16;
		SSI1_CR1_R |= SSI_CR1_SSE;            // enable SSI
		
		while((SSI1_SR_R&SSI_SR_TNF)==0){};   // wait until transmit FIFO not full
		SSI1_DR_R = data;                        // data out

}

// --------------     DAC_Out   --------------------------------------------
// Send data to TLV5616 12-bit DAC
// inputs:  voltage output (0 to 4095)
// 
void DAC_Out(uint16_t code){
    // write this
    // Consider the following registers:
	  // SSI1_SR_R, SSI1_DR_R
		while((SSI1_SR_R&SSI_SR_TNF)==0){};   // wait until transmit FIFO not full
		SSI1_DR_R = code;                        // data out
}

// --------------     DAC_OutNonBlocking   ------------------------------------
// Send data to TLV5616 12-bit DAC without checking for room in the FIFO
// inputs:  voltage output (0 to 4095)
// 
void DAC_Out_NB(uint32_t code){
    // Consider writing this (If it is what your heart desires)
    // Consider the following registers:
	  // SSI1_SR_R, SSI1_DR_R
		SSI1_DR_R = code;                        // data out
}

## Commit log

2024-12-09 Create Beginning
2024-12-10 lalla
2024-12-10 moving to baemax folder
2024-12-10 some more updates idk
2024-12-10 added alarm clock

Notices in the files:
Baemax/sw/inc/ST7735.c:
MIT license, all text above must be included in any redistribution
ISBN: 978-1463590154, Jonathan Valvano, copyright (c) 2016
Copyright 2016 by Jonathan W. Valvano, valvano@mail.utexas.edu
